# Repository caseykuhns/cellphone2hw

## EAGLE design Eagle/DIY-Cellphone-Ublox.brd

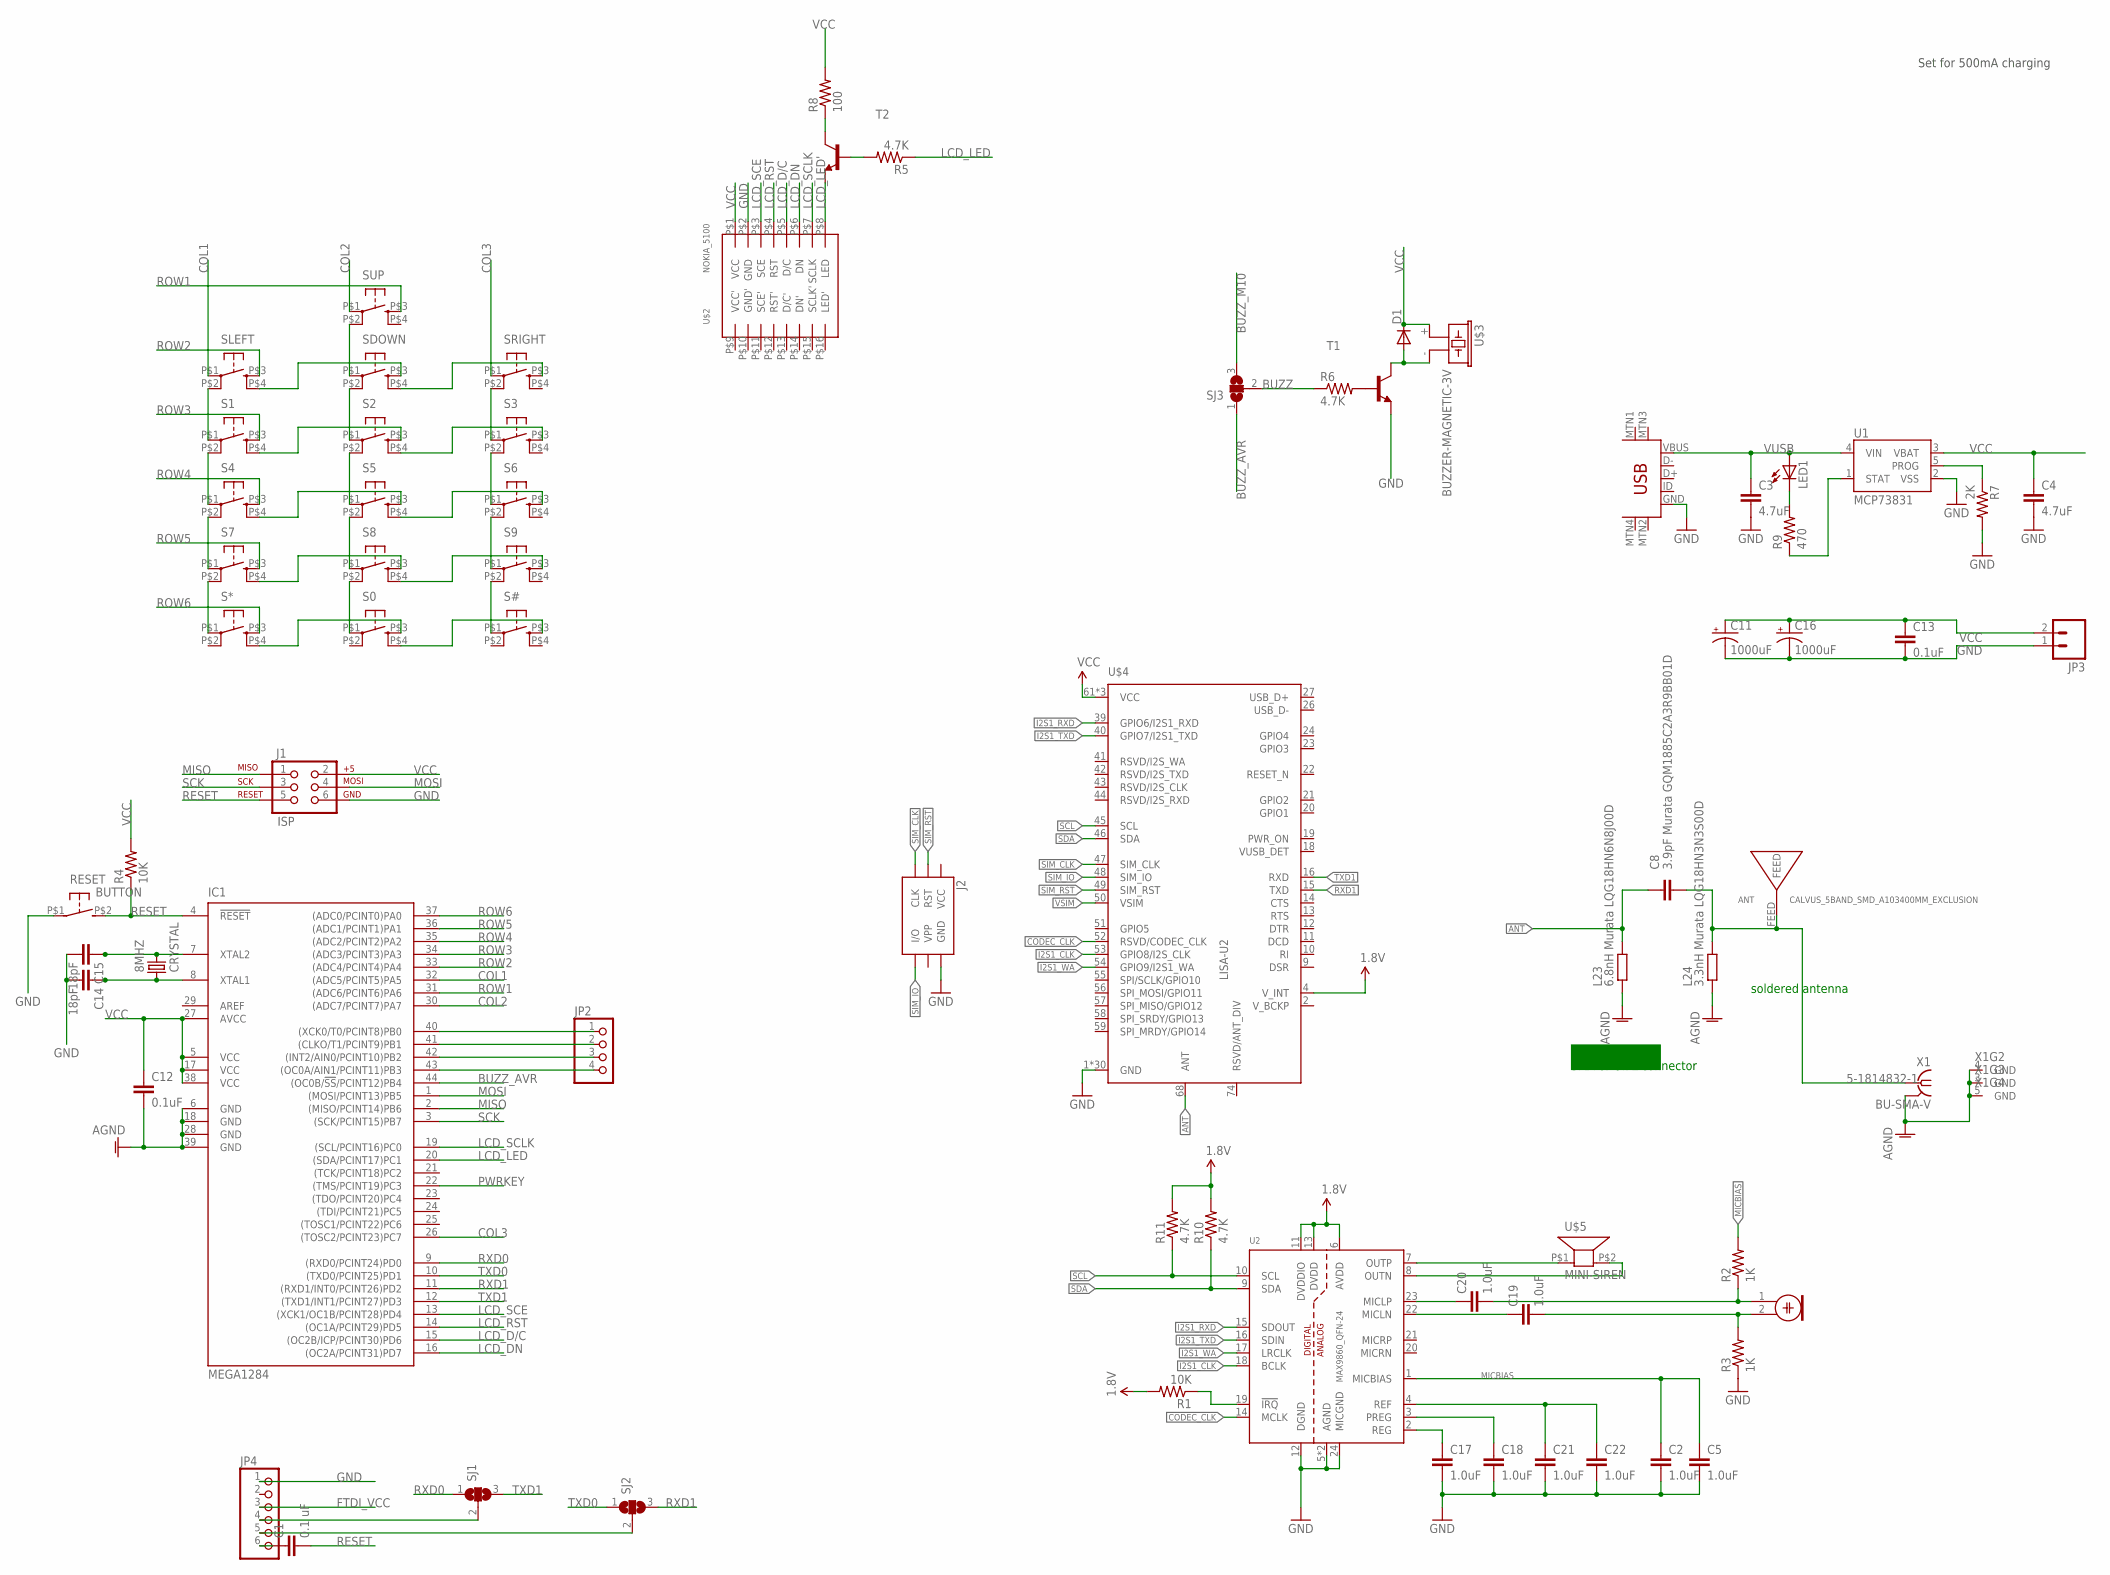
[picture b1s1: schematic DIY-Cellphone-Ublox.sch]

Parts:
8MHZ: CRYSTAL; 2-SMD-5X3MM
ANT: CALVUS_5BAND_SMD_A103400MM_EXCLUSION; CALVUS_5BAND_SMD_A10340_0MM_EXCLUSION
C1: 0.1 uF; C1206
C2, C5, C17, C18, C19, C20, C21, C22: 1.0uF; 0603-CAP
C3, C4: 4.7uF; C1206
C8: 3.9pF Murata GQM1885C2A3R9BB01D; C0603-ROUND
C11, C16: 1000uF; D/7343-31R
C12, C13: 0.1uF; C1206
C14, C15: 18pF; C1206
D1: DIODE-SOD123; SOD123
IC1: MEGA1284; TQFP44
J1: ISP; 2X3-NS
J2: SIMHOLDERSIM; SIMHOLDER
JP2: PINHD-1X4; 1X04
JP3: M02-JST-2MM-SMT; JST-2-SMD
JP4: PINHD-1X6/90; 1X06/90
L23: 6.8nH Murata LQG18HN6N8J00D; R0603-ROUND
L24: 3.3nH Murata LQG18HN3N3S00D; R0603-ROUND
LED1: LEDSMT1206; 1206
MIC: ELECTRET_MICROPHON-WM-64PC/64PK; WM-64PC/64PK
R1, R4: 10K; R1206
R2, R3: 1K; 0603-RES
R5, R6: 4.7K; R1206
R7: 2K; R1206
R8: 100; R1206
R9: 470; R1206
R10, R11: 4.7K; 0603-RES
RESET: BUTTON; B3U-1000P
S0, S1, S2, S3, S4, S5, S6, S7, S8, S9: SWITCH-JLEAD; BUTTON_6MM_JLEAD
S#: SWITCH-JLEAD; BUTTON_6MM_JLEAD
S*: SWITCH-JLEAD; BUTTON_6MM_JLEAD
SDOWN: SWITCH-JLEAD; BUTTON_6MM_JLEAD
SJ1, SJ2, SJ3: SJ2W; SJ_2
SLEFT: SWITCH-JLEAD; BUTTON_6MM_JLEAD
SRIGHT: SWITCH-JLEAD; BUTTON_6MM_JLEAD
SUP: SWITCH-JLEAD; BUTTON_6MM_JLEAD
T1, T2: MMBT3904LT1-NPN-SOT23-BEC; SOT23-BEC
U1: MCP73831; SOT23-5
U2: MAX9860_QFN-24; QFN-24_MAXIM_90-0022
U$1: USB-MINIB-5PIN; USB-MINIB
U$2: NOKIA_5100; NOKIA_5100_SPARKFUN
U$3: BUZZER-MAGNETIC-3V; PUI-SMT-0540
U$4: LISA-U2
U$5: MINI-SIREN; SPEAKER-6.4MM
X1: BU-SMA-V

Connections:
1.8V: R1.2, R10.2, R11.2, U2.6 (AVDD), U2.11 (DVDDIO), U2.13 (DVDD), U$4.4 (V_INT)
ANT: C8.1, L23.2, U$4.68 (ANT)
ANTENA: ANT.FEED, C8.2, L24.2, X1.1
AREF: IC1.29 (AREF)
BUZZ: R6.1, SJ3.2
BUZZ_AVR: IC1.44 ((OC0B/!SS!/PCINT12)PB4), SJ3.1
BUZZ_M10: SJ3.3
CODEC_CLK: U2.14 (MCLK), U$4.52 (RSVD/CODEC_CLK)
COL1: IC1.32 ((ADC5/PCINT5)PA5), SLEFT.P$1
COL2: IC1.30 ((ADC7/PCINT7)PA7), SUP.P$1
COL3: IC1.26 ((TOSC2/PCINT23)PC7), SRIGHT.P$1
FTDI_VCC: JP4.3
GND: C2.2, C3.2, C4.2, C5.2, C11.-, C12.2, C13.2, C14.2, C15.2, C16.-, C17.2, C18.2, C21.2, C22.2, IC1.6 (GND), IC1.18 (GND), IC1.28 (GND), IC1.39 (GND), J1.6, J2.C5 (GND), JP3.1 (2), JP4.1, L23.1, L24.1, R3.1, R7.2, RESET.P$1, T1.E, U1.2 (VSS), U2.5 (AGND), U2.12 (DGND), U2.24 (MICGND), U2.EP (AGND), U$1.GND, U$2.P$2 (GND), U$4.1 (GND), U$4.3 (GND), U$4.6 (GND), U$4.7 (GND), U$4.8 (GND), U$4.17 (GND), U$4.25 (GND), U$4.28 (GND), U$4.29 (GND), U$4.30 (GND), U$4.31 (GND), U$4.32 (GND), U$4.33 (GND), U$4.34 (GND), U$4.35 (GND), U$4.36 (GND), U$4.37 (GND), U$4.38 (GND), U$4.60 (GND), U$4.64 (GND), U$4.65 (GND), U$4.66 (GND), U$4.67 (GND), U$4.69 (GND), U$4.70 (GND), U$4.71 (GND), U$4.72 (GND), U$4.73 (GND), U$4.75 (GND), U$4.76 (GND), X1.2 (GND), X1.3 (GND), X1.4 (GND), X1.5 (GND)
I2S1_CLK: U2.18 (BCLK), U$4.53 (GPIO8/I2S_CLK)
I2S1_RXD: U2.15 (SDOUT), U$4.39 (GPIO6/I2S1_RXD)
I2S1_TXD: U2.16 (SDIN), U$4.40 (GPIO7/I2S1_TXD)
I2S1_WA: U2.17 (LRCLK), U$4.54 (GPIO9/I2S1_WA)
LCD_D/C: IC1.15 ((OC2B/ICP/PCINT30)PD6), U$2.P$5 (D/C)
LCD_DN: IC1.16 ((OC2A/PCINT31)PD7), U$2.P$6 (DN)
LCD_LED: IC1.20 ((SDA/PCINT17)PC1), R5.1
LCD_LED': T2.E, U$2.P$8 (LED)
LCD_RST: IC1.14 ((OC1A/PCINT29)PD5), U$2.P$4 (RST)
LCD_SCE: IC1.13 ((XCK1/OC1B/PCINT28)PD4), U$2.P$3 (SCE)
LCD_SCLK: IC1.19 ((SCL/PCINT16)PC0), U$2.P$7 (SCLK)
MICBIAS: C2.1, C5.1, R2.2, U2.1 (MICBIAS)
MISO: IC1.2 ((MISO/PCINT14)PB6), J1.1
MOSI: IC1.1 ((MOSI/PCINT13)PB5), J1.4
unnamed: C20.1, U2.23 (MICLP)
unnamed: R5.2, T2.B
unnamed: R8.1, T2.C
unnamed: D1.A, T1.C, U$3.- (2)
unnamed: C1.1, JP4.6
unnamed: R6.2, T1.B
unnamed: 8MHZ.P$2 (2), C15.1, IC1.7 (XTAL2)
unnamed: 8MHZ.P$1 (1), C14.1, IC1.8 (XTAL1)
unnamed: C19.1, U2.22 (MICLN)
unnamed: S1.P$1, SLEFT.P$2 (P1)
unnamed: S1.P$2 (P1), S4.P$1
unnamed: S4.P$2 (P1), S7.P$1
unnamed: JP4.4, SJ1.2
unnamed: SDOWN.P$1, SUP.P$2 (P1)
unnamed: S2.P$1, SDOWN.P$2 (P1)
unnamed: S2.P$2 (P1), S5.P$1
unnamed: S5.P$2 (P1), S8.P$1
unnamed: JP4.5, SJ2.2
unnamed: S3.P$1, SRIGHT.P$2 (P1)
unnamed: S3.P$2 (P1), S6.P$1
unnamed: S6.P$2 (P1), S9.P$1
unnamed: S0.P$4 (S1), S#.P$3 (S)
unnamed: S0.P$3 (S), S*.P$4 (S1)
unnamed: S7.P$4 (S1), S8.P$3 (S)
unnamed: S8.P$4 (S1), S9.P$3 (S)
unnamed: S4.P$4 (S1), S5.P$3 (S)
unnamed: S5.P$4 (S1), S6.P$3 (S)
unnamed: S1.P$4 (S1), S2.P$3 (S)
unnamed: S2.P$4 (S1), S3.P$3 (S)
unnamed: SDOWN.P$3 (S), SLEFT.P$4 (S1)
unnamed: SDOWN.P$4 (S1), SRIGHT.P$3 (S)
unnamed: S7.P$2 (P1), S*.P$1
unnamed: S0.P$1, S8.P$2 (P1)
unnamed: S9.P$2 (P1), S#.P$1
unnamed: R9.1, U1.1 (STAT)
unnamed: LED1.C, R9.2
unnamed: C20.2, MIC.1, R2.1
unnamed: IC1.40 ((XCK0/T0/PCINT8)PB0), JP2.1
unnamed: IC1.41 ((CLKO/T1/PCINT9)PB1), JP2.2
unnamed: IC1.42 ((INT2/AIN0/PCINT10)PB2), JP2.3
unnamed: IC1.43 ((OC0A/AIN1/PCINT11)PB3), JP2.4
unnamed: C19.2, MIC.2, R3.2
unnamed: R1.1, U2.19 (!IRQ)
unnamed: C21.1, C22.1, U2.4 (REF)
unnamed: U2.7 (OUTP), U$5.P$1 (1)
unnamed: U2.8 (OUTN), U$5.P$2 (2)
unnamed: C17.1, U2.2 (REG)
unnamed: C18.1, U2.3 (PREG)
PROG: R7.1, U1.5 (PROG)
PWRKEY: IC1.22 ((TMS/PCINT19)PC3)
RESET: C1.2, IC1.4 (!RESET), J1.5, R4.1, RESET.P$2 (S)
ROW1: IC1.31 ((ADC6/PCINT6)PA6), SUP.P$3 (S)
ROW2: IC1.33 ((ADC4/PCINT4)PA4), SLEFT.P$3 (S)
ROW3: IC1.34 ((ADC3/PCINT3)PA3), S1.P$3 (S)
ROW4: IC1.35 ((ADC2/PCINT2)PA2), S4.P$3 (S)
ROW5: IC1.36 ((ADC1/PCINT1)PA1), S7.P$3 (S)
ROW6: IC1.37 ((ADC0/PCINT0)PA0), S*.P$3 (S)
RXD0: IC1.9 ((RXD0/PCINT24)PD0), SJ1.1
RXD1: IC1.11 ((RXD1/INT0/PCINT26)PD2), SJ2.3, U$4.15 (TXD)
SCK: IC1.3 ((SCK/PCINT15)PB7), J1.3
SCL: R11.1, U2.10 (SCL), U$4.45 (SCL)
SDA: R10.1, U2.9 (SDA), U$4.46 (SDA)
SIM_CLK: J2.C3 (CLK), U$4.47 (SIM_CLK)
SIM_IO: J2.C7 (I/O), U$4.48 (SIM_IO)
SIM_RST: J2.C2 (RST), U$4.49 (SIM_RST)
TXD0: IC1.10 ((TXD0/PCINT25)PD1), SJ2.1
TXD1: IC1.12 ((TXD1/INT1/PCINT27)PD3), SJ1.3, U$4.16 (RXD)
VCC: C4.1, C11.+, C12.1, C13.1, C16.+, D1.C, IC1.5 (VCC), IC1.17 (VCC), IC1.27 (AVCC), IC1.38 (VCC), J1.2, J2.C1 (VCC), JP3.2 (1), R4.2, R8.2, U1.3 (VBAT), U$2.P$1 (VCC), U$3.+ (1), U$4.61 (VCC), U$4.62 (VCC), U$4.63 (VCC)
VSIM: U$4.50 (VSIM)
VUSB: C3.1, LED1.A, U1.4 (VIN), U$1.VBUS

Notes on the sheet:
soldered antenna
SMA or U.FL connector
Set for 500mA charging

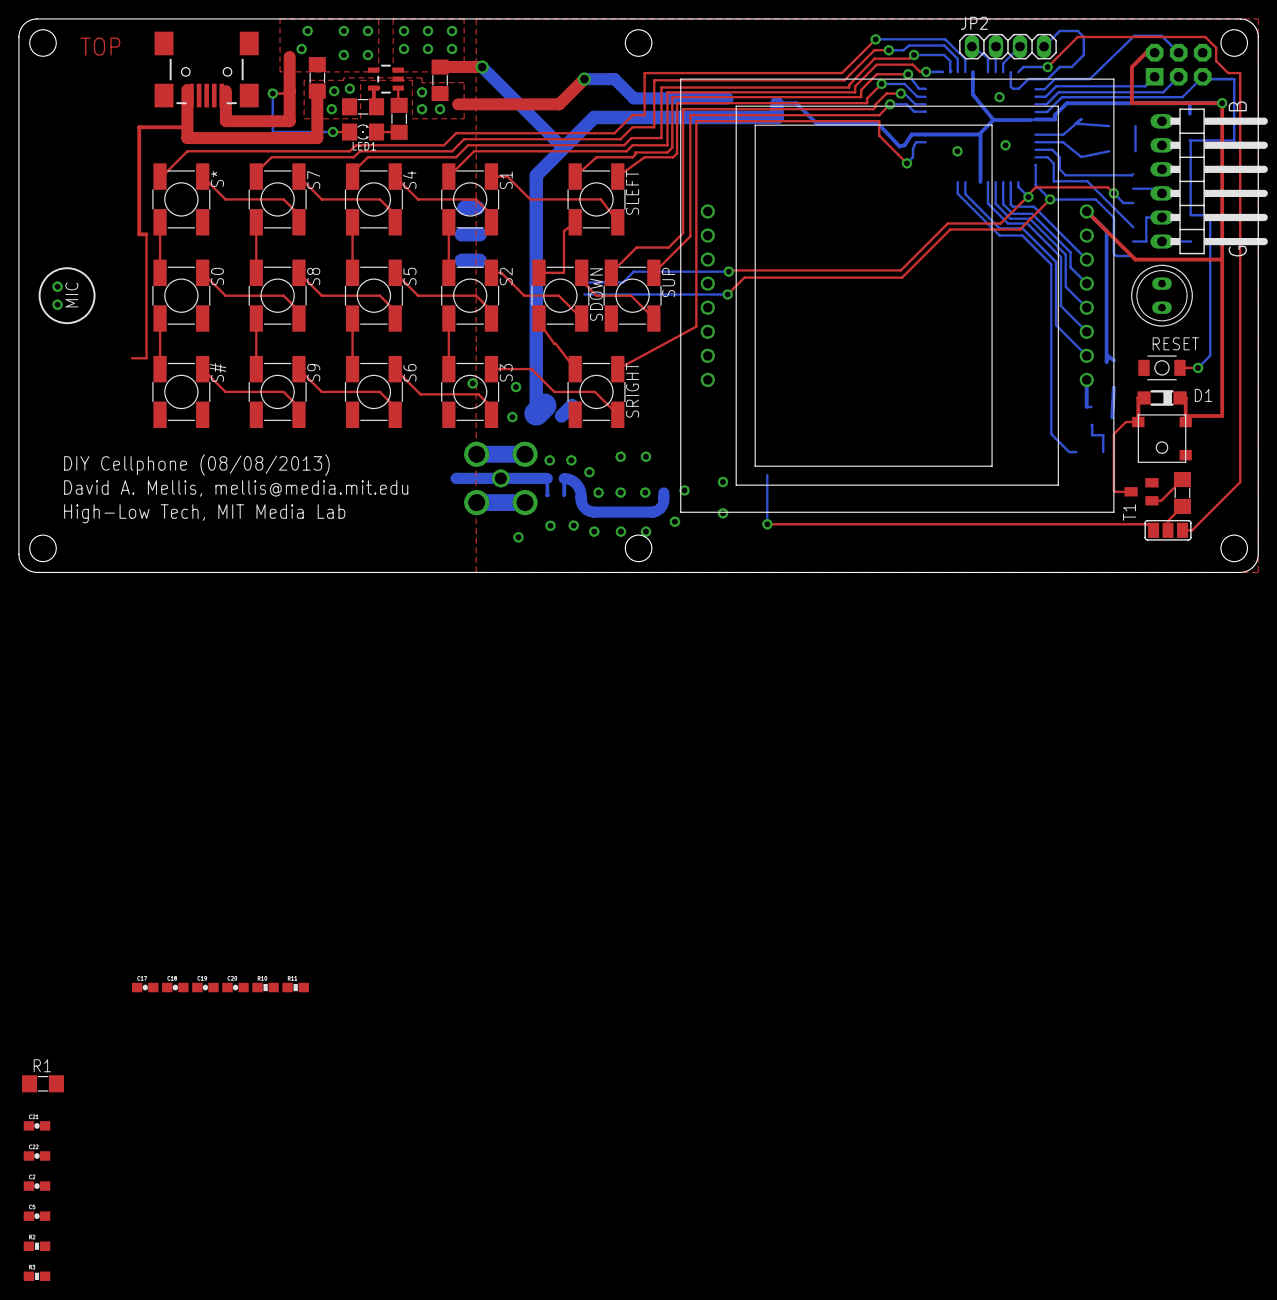
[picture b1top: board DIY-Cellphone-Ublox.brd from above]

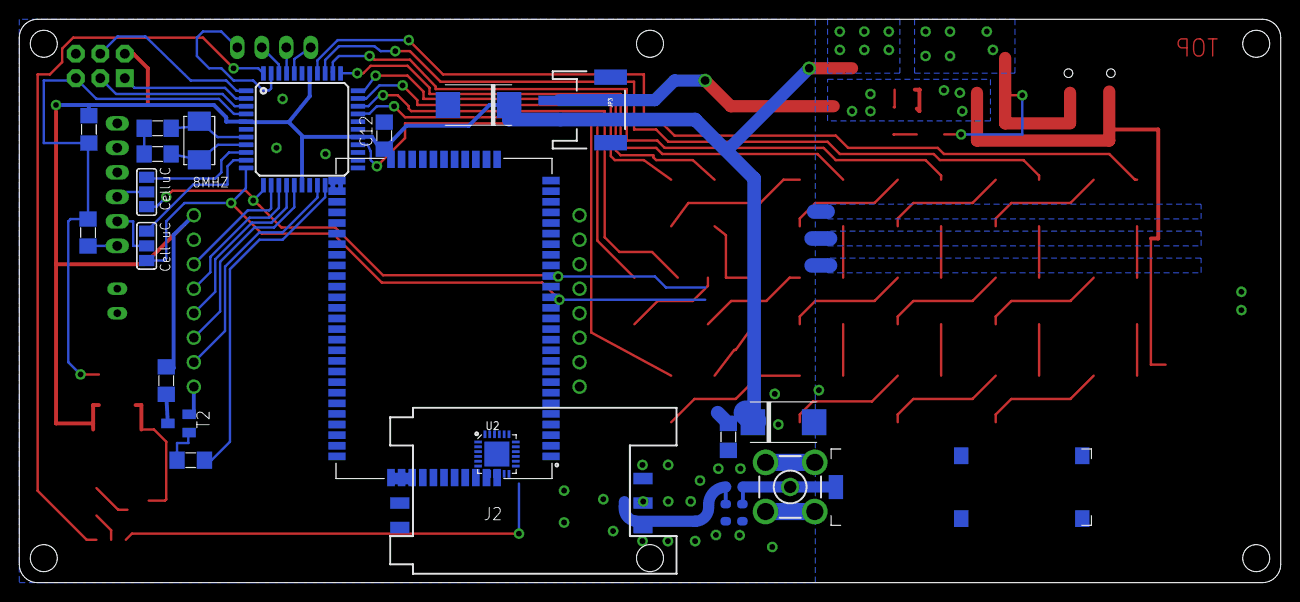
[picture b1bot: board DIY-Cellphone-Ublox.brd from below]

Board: 2 copper layers, 130.8 x 58.4 mm, 72 parts (24 on the bottom side), 92 nets.

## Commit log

2015-10-28 added new module
2015-11-19 added module to cellphone board

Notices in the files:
parts and their libraries:
SparkFun-Connectors: Licensing: CC v3.0 Share-Alike You are welcome to use this library for commercial purposes.
SparkFun-Resistors: Licensing: Creative Commons ShareAlike 4.0 International - https://creativecommons.org/licenses/by-sa/4.0
